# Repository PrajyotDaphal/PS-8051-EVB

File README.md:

# PS-8051-EVB  
**8051 Microcontroller Evaluation Board**

## 📌 Project Overview
PS-8051-EVB is a custom-designed **8051 microcontroller evaluation board** developed for embedded systems learning and prototyping. The board integrates a regulated 5V power supply, USB-to-UART communication using FT232RL, crystal oscillator, reset circuitry, and multiple 2.54 mm IDC connectors for external interfacing.

## ⚙️ Key Features
- 8051 microcontroller (40-pin DIP / ZIF socket compatible)
- Onboard 5V regulated power supply (L7805)
- USB-to-UART interface using FT232RL
- External crystal oscillator circuit
- Reset circuitry for reliable startup
- 2.54 mm IDC headers for I/O expansion
- Mounting holes for enclosure fitting

## 🛠 Tools Used
- KiCad EDA (Schematic & PCB Layout)

## 📐 Design Files
- Complete KiCad schematic and PCB layout
- Manufacturing-ready Gerber files
- Project images and documentation

## 🖼 Schematic

## 🧩| Full Layout | Upper Copper | Lower Copper |

## 🔷 PCB 3D View

## 📂 Repository Structure
PS-8051-EVB/
├─ kicad/
├─ images/
├─ gerber/
├─ bom/
└─ README.md

## 🎯 Applications
- Embedded systems learning
- 8051 microcontroller experiments
- USB-based serial communication projects
- Academic and training use

## 👤 Author
**Prajyot Daphal**  
ENTC Engineering Student

---

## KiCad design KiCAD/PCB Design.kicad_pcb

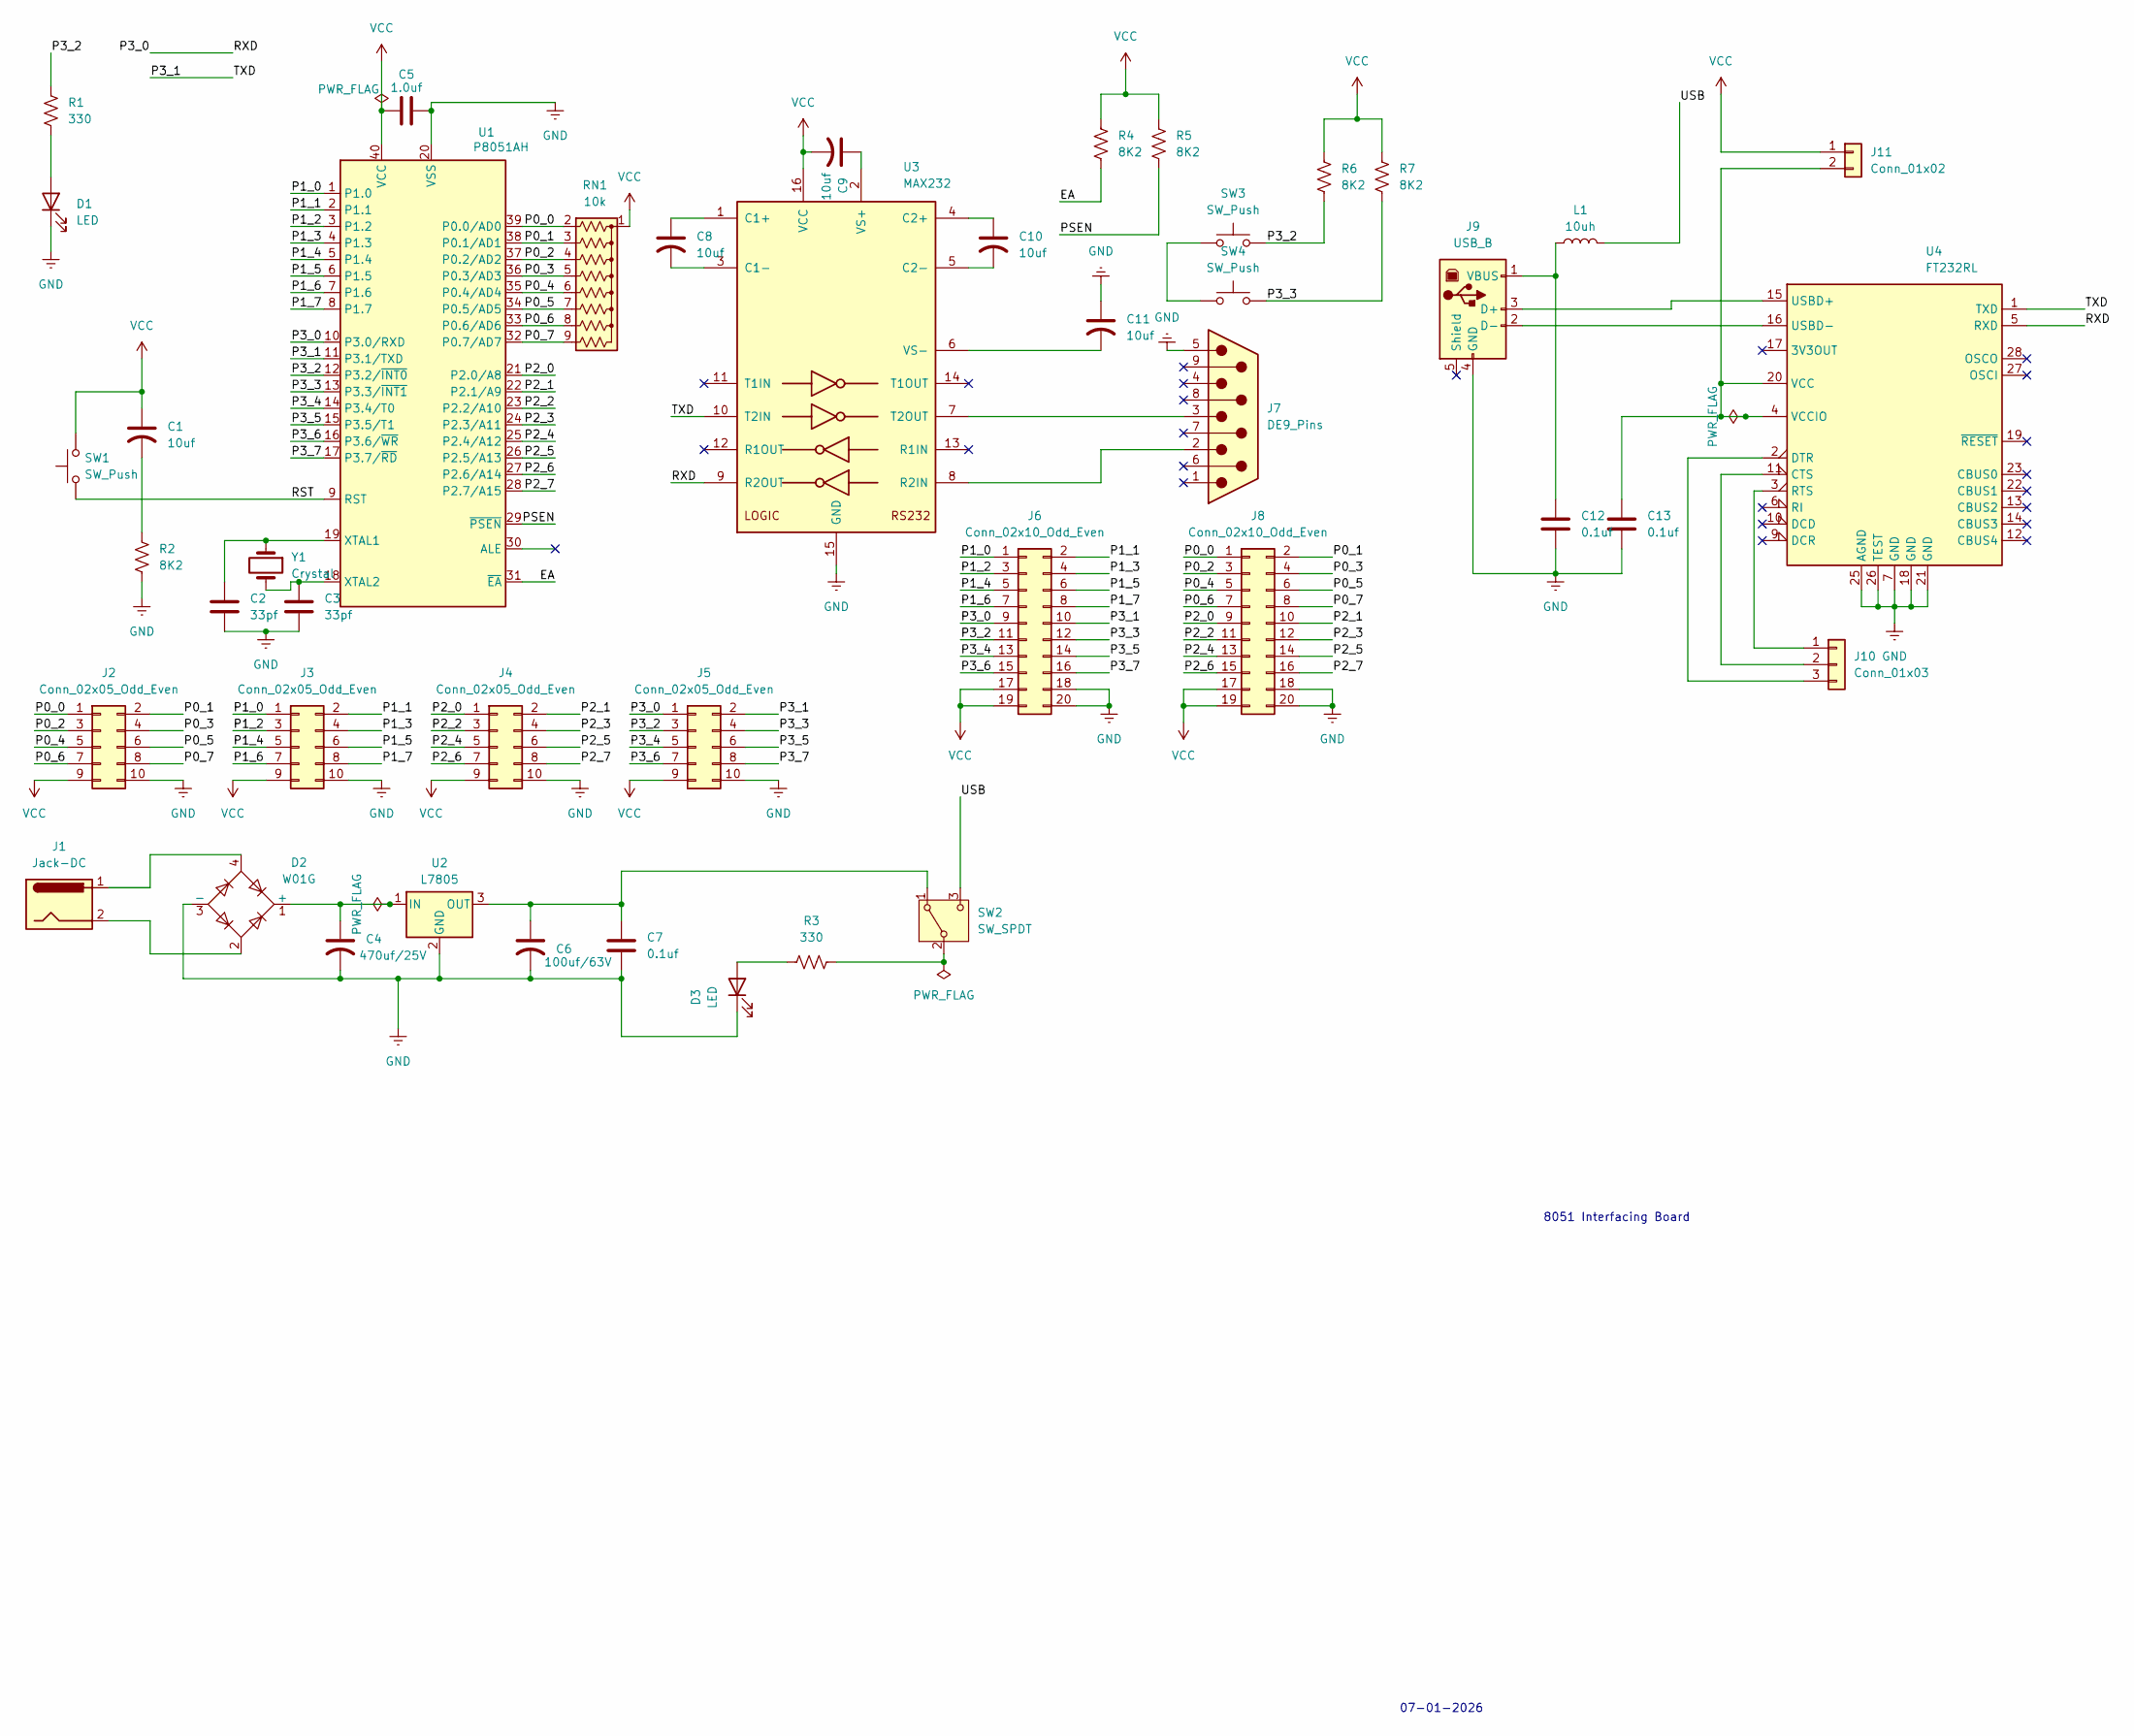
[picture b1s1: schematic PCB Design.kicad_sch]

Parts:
C1, C8, C9, C10, C11: 10uf; CP_Radial_D5.0mm_P2.50mm
C2, C3: 33pf; C_Disc_D6.0mm_W2.5mm_P5.00mm
C4: 470uf/25V; CP_Radial_D6.3mm_P2.50mm
C5: 1.0uf; C_Disc_D7.5mm_W2.5mm_P5.00mm
C6: 100uf/63V; CP_Radial_D6.3mm_P2.50mm
C7: 0.1uf; C_Disc_D7.0mm_W2.5mm_P5.00mm
C12, C13: 0.1uf; C_Disc_D7.5mm_W2.5mm_P5.00mm
D1, D3: LED; LED_D3.0mm
D2: W01G; Diode_Bridge_Round_D9.8mm
J1: Jack-DC; BarrelJack_Horizontal
J2, J3, J4, J5: Conn_02x05_Odd_Even; IDC-Header_2x05_P2.54mm_Vertical
J6, J8: Conn_02x10_Odd_Even; IDC-Header_2x11_P2.54mm_Vertical
J7: DE9_Pins; DSUB-9_Pins_Horizontal_P2.77x2.84mm_EdgePinOffset7.70mm_Hou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
J9: USB_B; USB_B_Lumberg_2411_02_Horizontal
J10: Conn_01x03; PinHeader_1x03_P2.54mm_Vertical
J11: Conn_01x02; PinHeader_1x02_P2.54mm_Vertical
L1: 10uh; L_0805_2012Metric
R1: 330; R_0805_2012Metric_Pad1.20x1.40mm_HandSolder
R2, R4, R5, R6: 8K2; R_Axial_DIN0204_L3.6mm_D1.6mm_P7.62mm_Horizontal
R3: 330; R_Axial_DIN0204_L3.6mm_D1.6mm_P7.62mm_Horizontal
R7: 8K2; R_0805_2012Metric
RN1: 10k; R_Array_SIP9
SW1, SW3, SW4: SW_Push; SW_PUSH_6mm
SW2: SW_SPDT; SW_Slide-03_Wuerth-WS-SLTV_10x2.5x6.4_P2.54mm
U1: P8051AH; DIP_Socket-40_W11.9mm_W12.7mm_W15.24mm_W17.78mm_W18.5mm_3M_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
U2: L7805; TO-220-3_Vertical
U3: MAX232; SMDIP-16_W7.62mm
U4: FT232RL; SSOP-28_5.3x10.2mm_P0.65mm
Y1: Crystal; Crystal_HC49-4H_Vertical

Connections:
/EA: R4.2, U1.31 (~EA)
/P0_0: J2.1, J8.1, RN1.2 (R1), U1.39 (P0.0/AD0)
/P0_1: J2.2, J8.2, RN1.3 (R2), U1.38 (P0.1/AD1)
/P0_2: J2.3, J8.3, RN1.4 (R3), U1.37 (P0.2/AD2)
/P0_3: J2.4, J8.4, RN1.5 (R4), U1.36 (P0.3/AD3)
/P0_4: J2.5, J8.5, RN1.6 (R5), U1.35 (P0.4/AD4)
/P0_5: J2.6, J8.6, RN1.7 (R6), U1.34 (P0.5/AD5)
/P0_6: J2.7, J8.7, RN1.8 (R7), U1.33 (P0.6/AD6)
/P0_7: J2.8, J8.8, RN1.9 (R8), U1.32 (P0.7/AD7)
/P1_0: J3.1, J6.1, U1.1 (P1.0)
/P1_1: J3.2, J6.2, U1.2 (P1.1)
/P1_2: J3.3, J6.3, U1.3 (P1.2)
/P1_3: J3.4, J6.4, U1.4 (P1.3)
/P1_4: J3.5, J6.5, U1.5 (P1.4)
/P1_5: J3.6, J6.6, U1.6 (P1.5)
/P1_6: J3.7, J6.7, U1.7 (P1.6)
/P1_7: J3.8, J6.8, U1.8 (P1.7)
/P2_0: J4.1, J8.9, U1.21 (P2.0/A8)
/P2_1: J4.2, J8.10, U1.22 (P2.1/A9)
/P2_2: J4.3, J8.11, U1.23 (P2.2/A10)
/P2_3: J4.4, J8.12, U1.24 (P2.3/A11)
/P2_4: J4.5, J8.13, U1.25 (P2.4/A12)
/P2_5: J4.6, J8.14, U1.26 (P2.5/A13)
/P2_6: J4.7, J8.15, U1.27 (P2.6/A14)
/P2_7: J4.8, J8.16, U1.28 (P2.7/A15)
/P3_0: J5.1, J6.9, U1.10 (P3.0/RXD), U3.9 (R2OUT), U4.5 (RXD)
/P3_1: J5.2, J6.10, U1.11 (P3.1/TXD), U3.10 (T2IN), U4.1 (TXD)
/P3_2: J5.3, J6.11, R1.1, R6.2, SW3.2, U1.12 (P3.2/~INT0)
/P3_3: J5.4, J6.12, R7.2, SW4.2, U1.13 (P3.3/~INT1)
/P3_4: J5.5, J6.13, U1.14 (P3.4/T0)
/P3_5: J5.6, J6.14, U1.15 (P3.5/T1)
/P3_6: J5.7, J6.15, U1.16 (P3.6/~WR)
/P3_7: J5.8, J6.16, U1.17 (P3.7/~RD)
/PSEN: R5.2, U1.29 (~PSEN)
/RST: SW1.1, U1.9 (RST)
/USB: L1.2, SW2.3 (C)
GND: C2.2, C3.2, C4.2, C5.2, C6.2, C7.2, C11.1, C12.2, C13.2, D1.1 (K), D2.3 (-), D3.1 (K), J2.10, J3.10, J4.10, J5.10, J6.18, J6.20, J7.5, J8.18, J8.20, J9.4 (GND), R2.2, U1.20 (VSS), U2.2 (GND), U3.15 (GND), U4.7 (GND), U4.18 (GND), U4.21 (GND), U4.25 (AGND), U4.26 (TEST)
unnamed: C1.2, R2.1
unnamed: D1.2 (A), R1.2
unnamed: C4.1, D2.1 (+), U2.1 (IN)
unnamed: D2.2, J1.2
unnamed: D2.4, J1.1
unnamed: D3.2 (A), R3.2
unnamed: J9.3 (D+), U4.15 (USBD+)
unnamed: J9.2 (D-), U4.16 (USBD-)
unnamed: C12.1, J9.1 (VBUS), L1.1
unnamed: J10.1, U4.3 (RTS)
unnamed: J10.2, U4.11 (CTS)
unnamed: J10.3, U4.2 (DTR)
unnamed: C13.1, J11.2, U4.4 (VCCIO), U4.20 (VCC)
unnamed: C6.1, C7.1, SW2.1 (A), U2.3 (OUT)
unnamed: R3.1, SW2.2 (B)
unnamed: SW3.1, SW4.1
unnamed: C2.1, U1.19 (XTAL1), Y1.1
unnamed: C3.1, U1.18 (XTAL2), Y1.2
unnamed: C8.1, U3.1 (C1+)
unnamed: C8.2, U3.3 (C1-)
unnamed: C10.1, U3.4 (C2+)
unnamed: C10.2, U3.5 (C2-)
unnamed: J7.2, U3.8 (R2IN)
unnamed: J7.3, U3.7 (T2OUT)
unnamed: C9.1, U3.2 (VS+)
unnamed: C11.2, U3.6 (VS-)
VCC: C1.1, C5.1, C9.2, J2.9, J3.9, J4.9, J5.9, J6.17, J6.19, J8.17, J8.19, J11.1, R4.1, R5.1, R6.1, R7.1, RN1.1 (common), SW1.2, U1.40 (VCC), U3.16 (VCC)

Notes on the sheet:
8051 Interfacing Board
07-01-2026

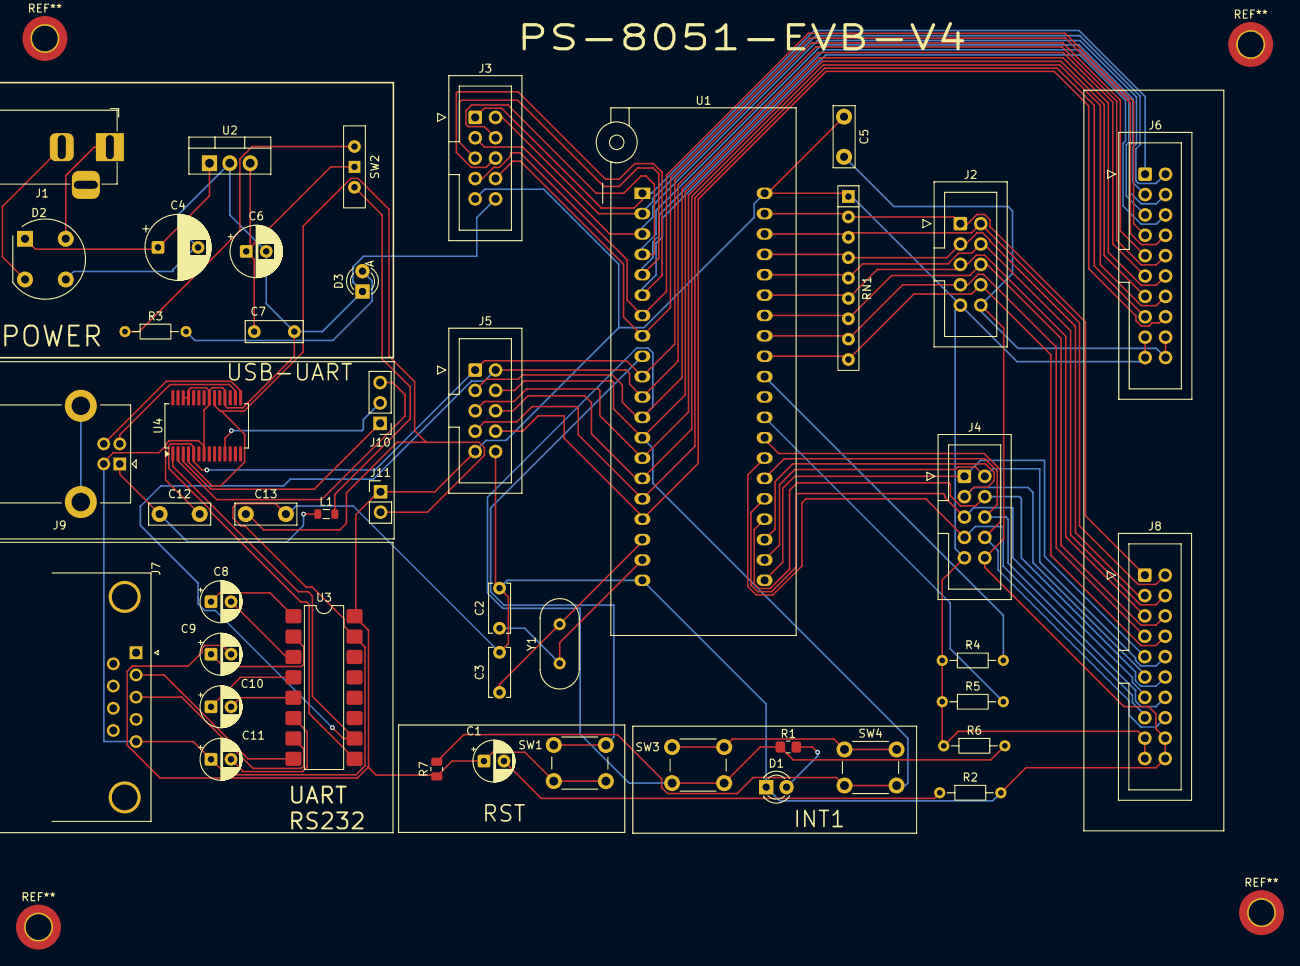
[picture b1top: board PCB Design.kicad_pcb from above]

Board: 2 copper layers, 45 parts (0 on the bottom side), 64 nets.

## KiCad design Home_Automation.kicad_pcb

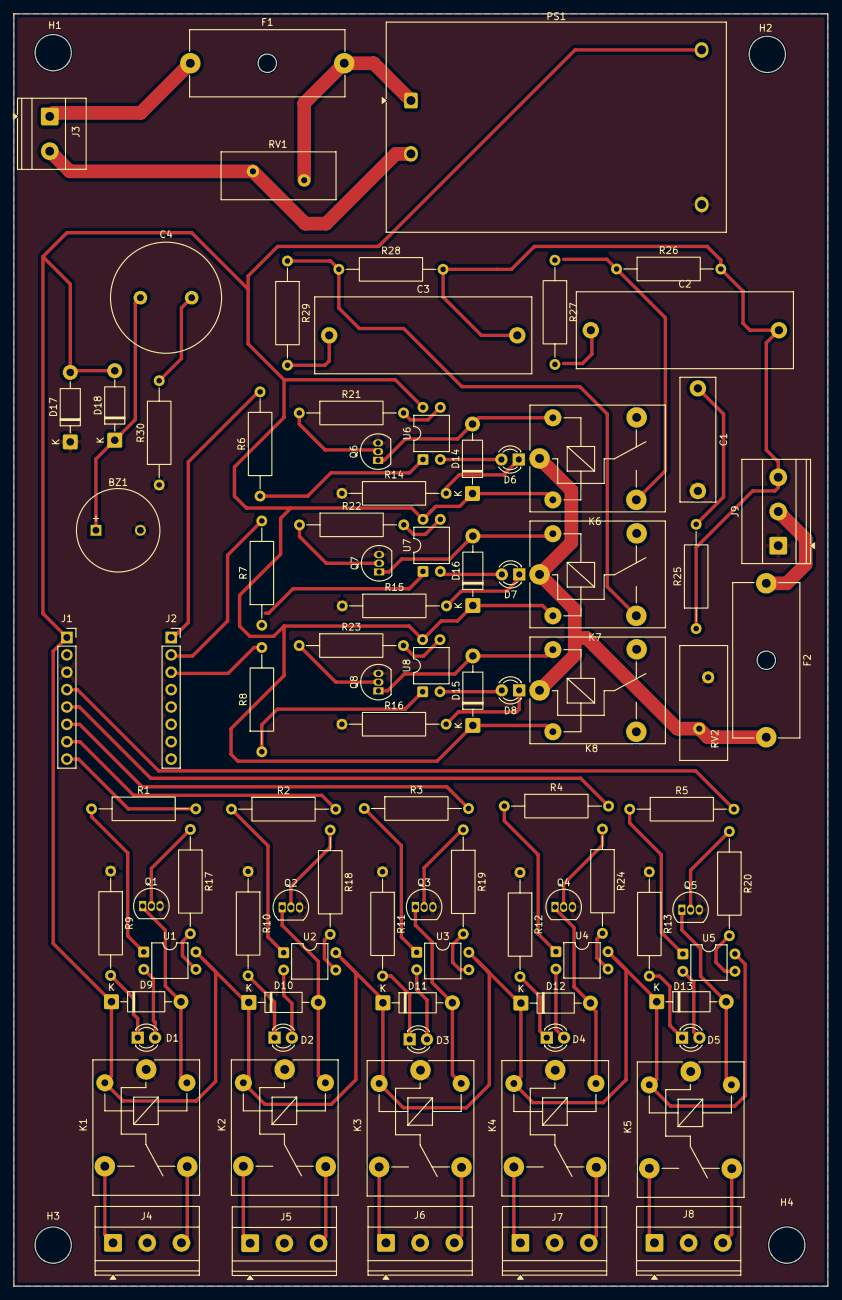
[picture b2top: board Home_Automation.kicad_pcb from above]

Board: 2 copper layers, 119.0 x 186.0 mm, 95 parts (0 on the bottom side), 80 nets.

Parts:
BZ1: Buzzer; MagneticBuzzer_ProSignal_ABT-410-RC
C1: 0.1µF X2 275VAC; C_Rect_L18.0mm_W5.0mm_P15.00mm_FKS3_FKP3
C2: 2.2uf/250V; C_Rect_L31.5mm_W11.0mm_P27.50mm_MKS4
C3: 3.3uf/250V; C_Rect_L31.5mm_W11.0mm_P27.50mm_MKS4
C4: 4700u; C_Radial_D16.0mm_H25.0mm_P7.50mm
D1, D2, D3, D4, D5, D6, D7, D8: LED; LED_D3.0mm
D9, D10, D11, D12, D13, D14, D15, D16: 1N4007; D_DO-41_SOD81_P10.16mm_Horizontal
D17, D18: 1N5819; D_DO-41_SOD81_P10.16mm_Horizontal
F1, F2: 250VAC/250mA; Fuseholder_Cylinder-5x20mm_Schurter_0031_8201_Horizontal_Op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
H1, H2, H3, H4: MountingHole; MountingHole_5.3mm_M5
J1, J2: Conn_01x08_Socket; PinSocket_1x08_P2.54mm_Vertical
J3: Screw_Terminal_01x02; TerminalBlock_Phoenix_MKDS-1,5-2-5.08_1x02_P5.08mm_Horizont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
J4, J5, J6, J7, J8, J9: Screw_Terminal_01x03; TerminalBlock_Phoenix_MKDS-1,5-3_1x03_P5.00mm_Horizontal
K1, K2, K3, K4, K5, K6, K7, K8: SANYOU_SRD_Form_C; Relay_SPDT_SANYOU_SRD_Series_Form_C
PS1: HLK-10M05; Converter_ACDC_Hi-Link_HLK-10Mxx
Q1, Q2, Q3, Q4, Q5, Q6, Q7, Q8: BC547; TO-92_Inline
R1, R2, R3, R4, R5, R6, R7, R8, R30: 330; R_Axial_DIN0309_L9.0mm_D3.2mm_P15.24mm_Horizontal
R9, R10, R11, R12, R13, R14, R15, R16, R17, R18, R19, R20, R21, R22, R23, R24: 1k; R_Axial_DIN0309_L9.0mm_D3.2mm_P15.24mm_Horizontal
R25: 100 (1/2, 1)W; R_Axial_DIN0309_L9.0mm_D3.2mm_P15.24mm_Horizontal
R26, R28: 220k 1/4W; R_Axial_DIN0309_L9.0mm_D3.2mm_P15.24mm_Horizontal
R27, R29: 2.2u/1/2W; R_Axial_DIN0309_L9.0mm_D3.2mm_P15.24mm_Horizontal
RV1, RV2: 471k; RV_Disc_D16.5mm_W6.7mm_P7.5mm
U1, U2, U3, U4, U5, U6, U7, U8: PC817; DIP-4_W7.62mm

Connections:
/0: J1.8, R1.2
/1: J1.7, R2.2
/2: J1.6, R3.2
/3: J1.5, R4.2
/4: J1.4, R5.2
/5: J2.1, R6.2
/6: J2.2, R7.2
/7: J2.3, R8.2
/9: J4.1, K1.3
/10: J5.1, K2.3
/11: J6.1, K3.3
/12: J7.1, K4.3
/13: J8.1, K5.3
/14: K6.3, R26.1, R27.1
/15: K7.3, R28.1, R29.1
/16: C2.2, C3.2, J9.3, K8.3, R25.1, R26.2, R28.2
/A: D9.2 (A), K1.5, Q1.1 (C)
/AC: F2.1, F2.2, J9.2, K6.1, K7.1, K8.1, RV2.2
/B: D10.2 (A), K2.5, Q2.1 (C)
/BUZZER: BZ1.1 (+), C4.1, D18.1 (K)
/C: D11.2 (A), K3.5, Q3.1 (C)
/D: D12.2 (A), K4.5, Q4.1 (C)
/E: D13.2 (A), K5.5, Q5.1 (C)
/F: D14.2 (A), K6.5, Q6.1 (C)
/G: D16.2 (A), K7.5, Q7.1 (C)
/H: D15.2 (A), K8.5, Q8.1 (C)
/VCC: D9.1 (K), D10.1 (K), D11.1 (K), D12.1 (K), D13.1 (K), D14.1 (K), D15.1 (K), D16.1 (K), D17.2 (A), D18.2 (A), J1.1, K1.2, K2.2, K3.2, K4.2, K5.2, K6.2, K7.2, K8.2, PS1.3 (-Vout), U1.4, U2.4, U3.4, U4.4, U5.4, U6.4, U7.4, U8.4
/i: J4.3, K1.4
/ii: J5.3, K2.4
/iii: J6.3, K3.4
/iv: J7.3, K4.4
/v: J8.3, K5.4
GND: BZ1.2 (-), C1.2, D17.1 (K), J1.3, J4.2, J5.2, J6.2, J7.2, J8.2, J9.1, K1.1, K2.1, K3.1, K4.1, K5.1, PS1.4 (+Vout), Q1.3 (E), Q2.3 (E), Q3.3 (E), Q4.3 (E), Q5.3 (E), Q6.3 (E), Q7.3 (E), Q8.3 (E), R9.1, R10.1, R11.1, R12.1, R13.1, R14.1, R15.1, R16.1, R30.1, RV2.1
unnamed: C1.1, R25.2
unnamed: C2.1, R27.2
unnamed: C3.1, R29.2
unnamed: C4.2, R30.2
unnamed: D1.2 (A), U1.2
unnamed: D1.1 (K), R9.2
unnamed: D2.2 (A), U2.2
unnamed: D2.1 (K), R10.2
unnamed: D3.2 (A), U3.2
unnamed: D3.1 (K), R11.2
unnamed: D4.2 (A), U4.2
unnamed: D4.1 (K), R12.2
unnamed: D5.2 (A), U5.2
unnamed: D5.1 (K), R13.2
unnamed: D6.2 (A), U6.2
unnamed: D6.1 (K), R14.2
unnamed: D7.2 (A), U7.2
unnamed: D7.1 (K), R15.2
unnamed: D8.2 (A), U8.2
unnamed: D8.1 (K), R16.2
unnamed: F1.1, J3.1
unnamed: J3.2, PS1.2 (AC/N), RV1.1
unnamed: F1.2, PS1.1 (AC/L), RV1.2
unnamed: Q1.2 (B), R17.1
unnamed: Q2.2 (B), R18.1
unnamed: Q3.2 (B), R19.1
unnamed: Q4.2 (B), R24.1
unnamed: Q5.2 (B), R20.1
unnamed: Q6.2 (B), R21.1
unnamed: Q7.2 (B), R22.1
unnamed: Q8.2 (B), R23.1
unnamed: R1.1, U1.1
unnamed: R2.1, U2.1
unnamed: R3.1, U3.1
unnamed: R4.1, U4.1
unnamed: R5.1, U5.1
unnamed: R6.1, U6.1
unnamed: R7.1, U7.1
unnamed: R8.1, U8.1
unnamed: R17.2, U1.3
unnamed: R18.2, U2.3
unnamed: R19.2, U3.3
unnamed: R20.2, U5.3
unnamed: R21.2, U6.3
unnamed: R22.2, U7.3
unnamed: R23.2, U8.3
unnamed: R24.2, U4.3

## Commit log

2026-01-07 Create KiCAD
2026-01-07 Initialize README for PS-8051-EVB project
    Added detailed project overview, features, tools, and applications for the PS-8051-EVB.
2026-01-07 Rename Screenshot 2026-01-07 213325.png to schematic.png
2026-01-07 Rename Screenshot 2026-01-07 212316.png to pcb_3d.png
2026-01-07 Rename Screenshot 2026-01-07 212248.png to pcb_layout.png
2026-02-15 png moves to Images
2026-02-15 Fix image paths in README.md
    Updated image paths in README for consistency.
2026-02-15 Revise PCB Layout section with image table
    Updated PCB Layout section to include images in a table format.
